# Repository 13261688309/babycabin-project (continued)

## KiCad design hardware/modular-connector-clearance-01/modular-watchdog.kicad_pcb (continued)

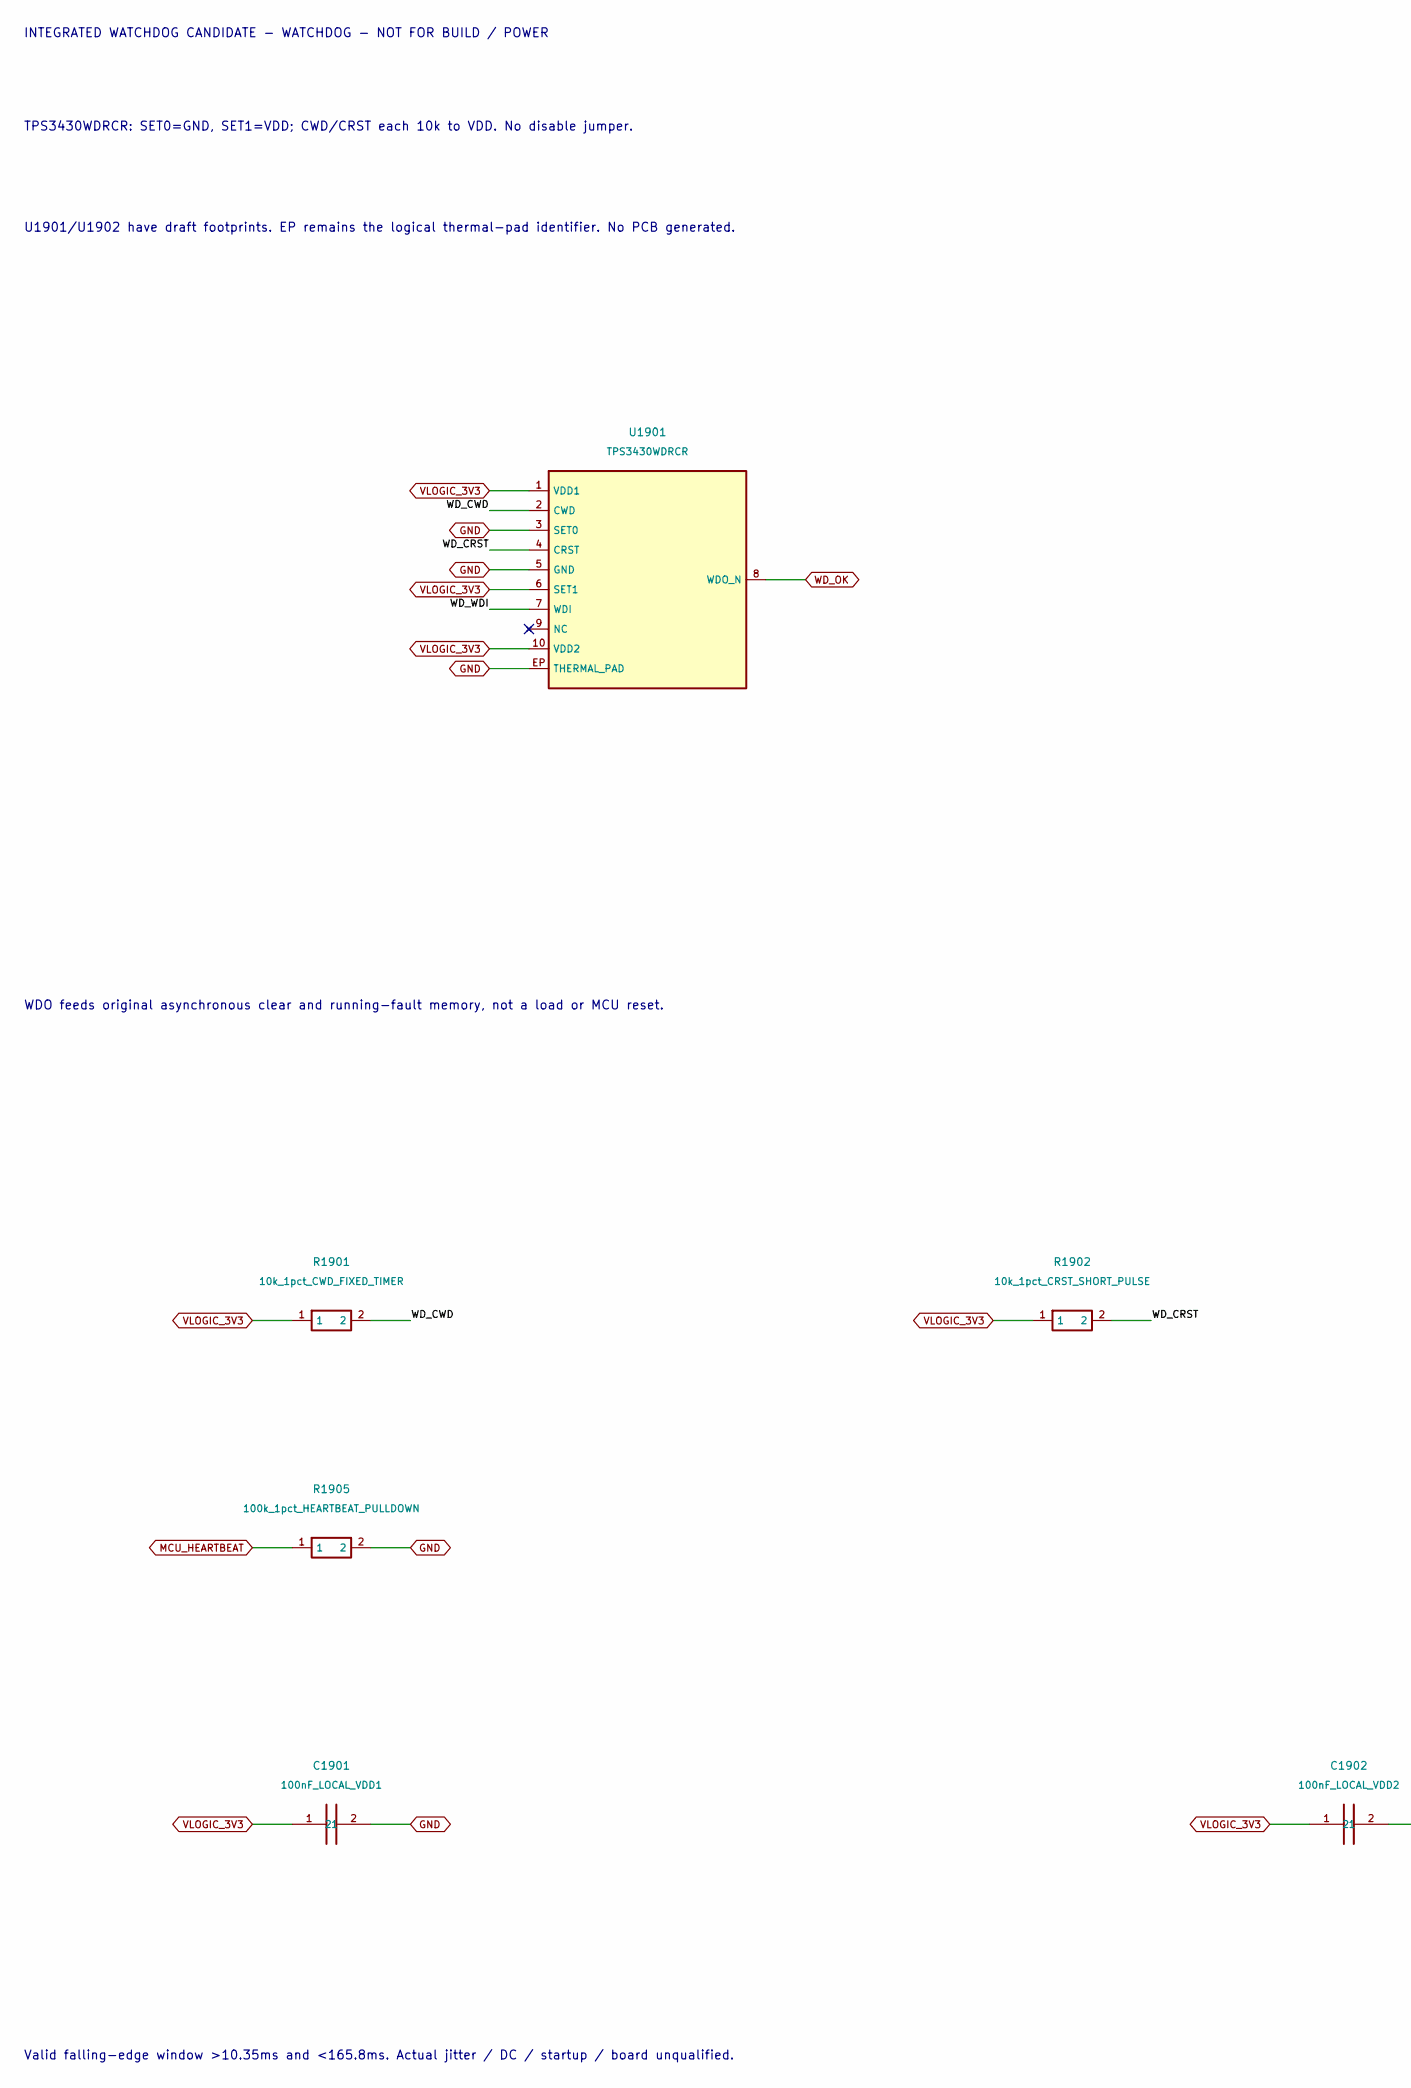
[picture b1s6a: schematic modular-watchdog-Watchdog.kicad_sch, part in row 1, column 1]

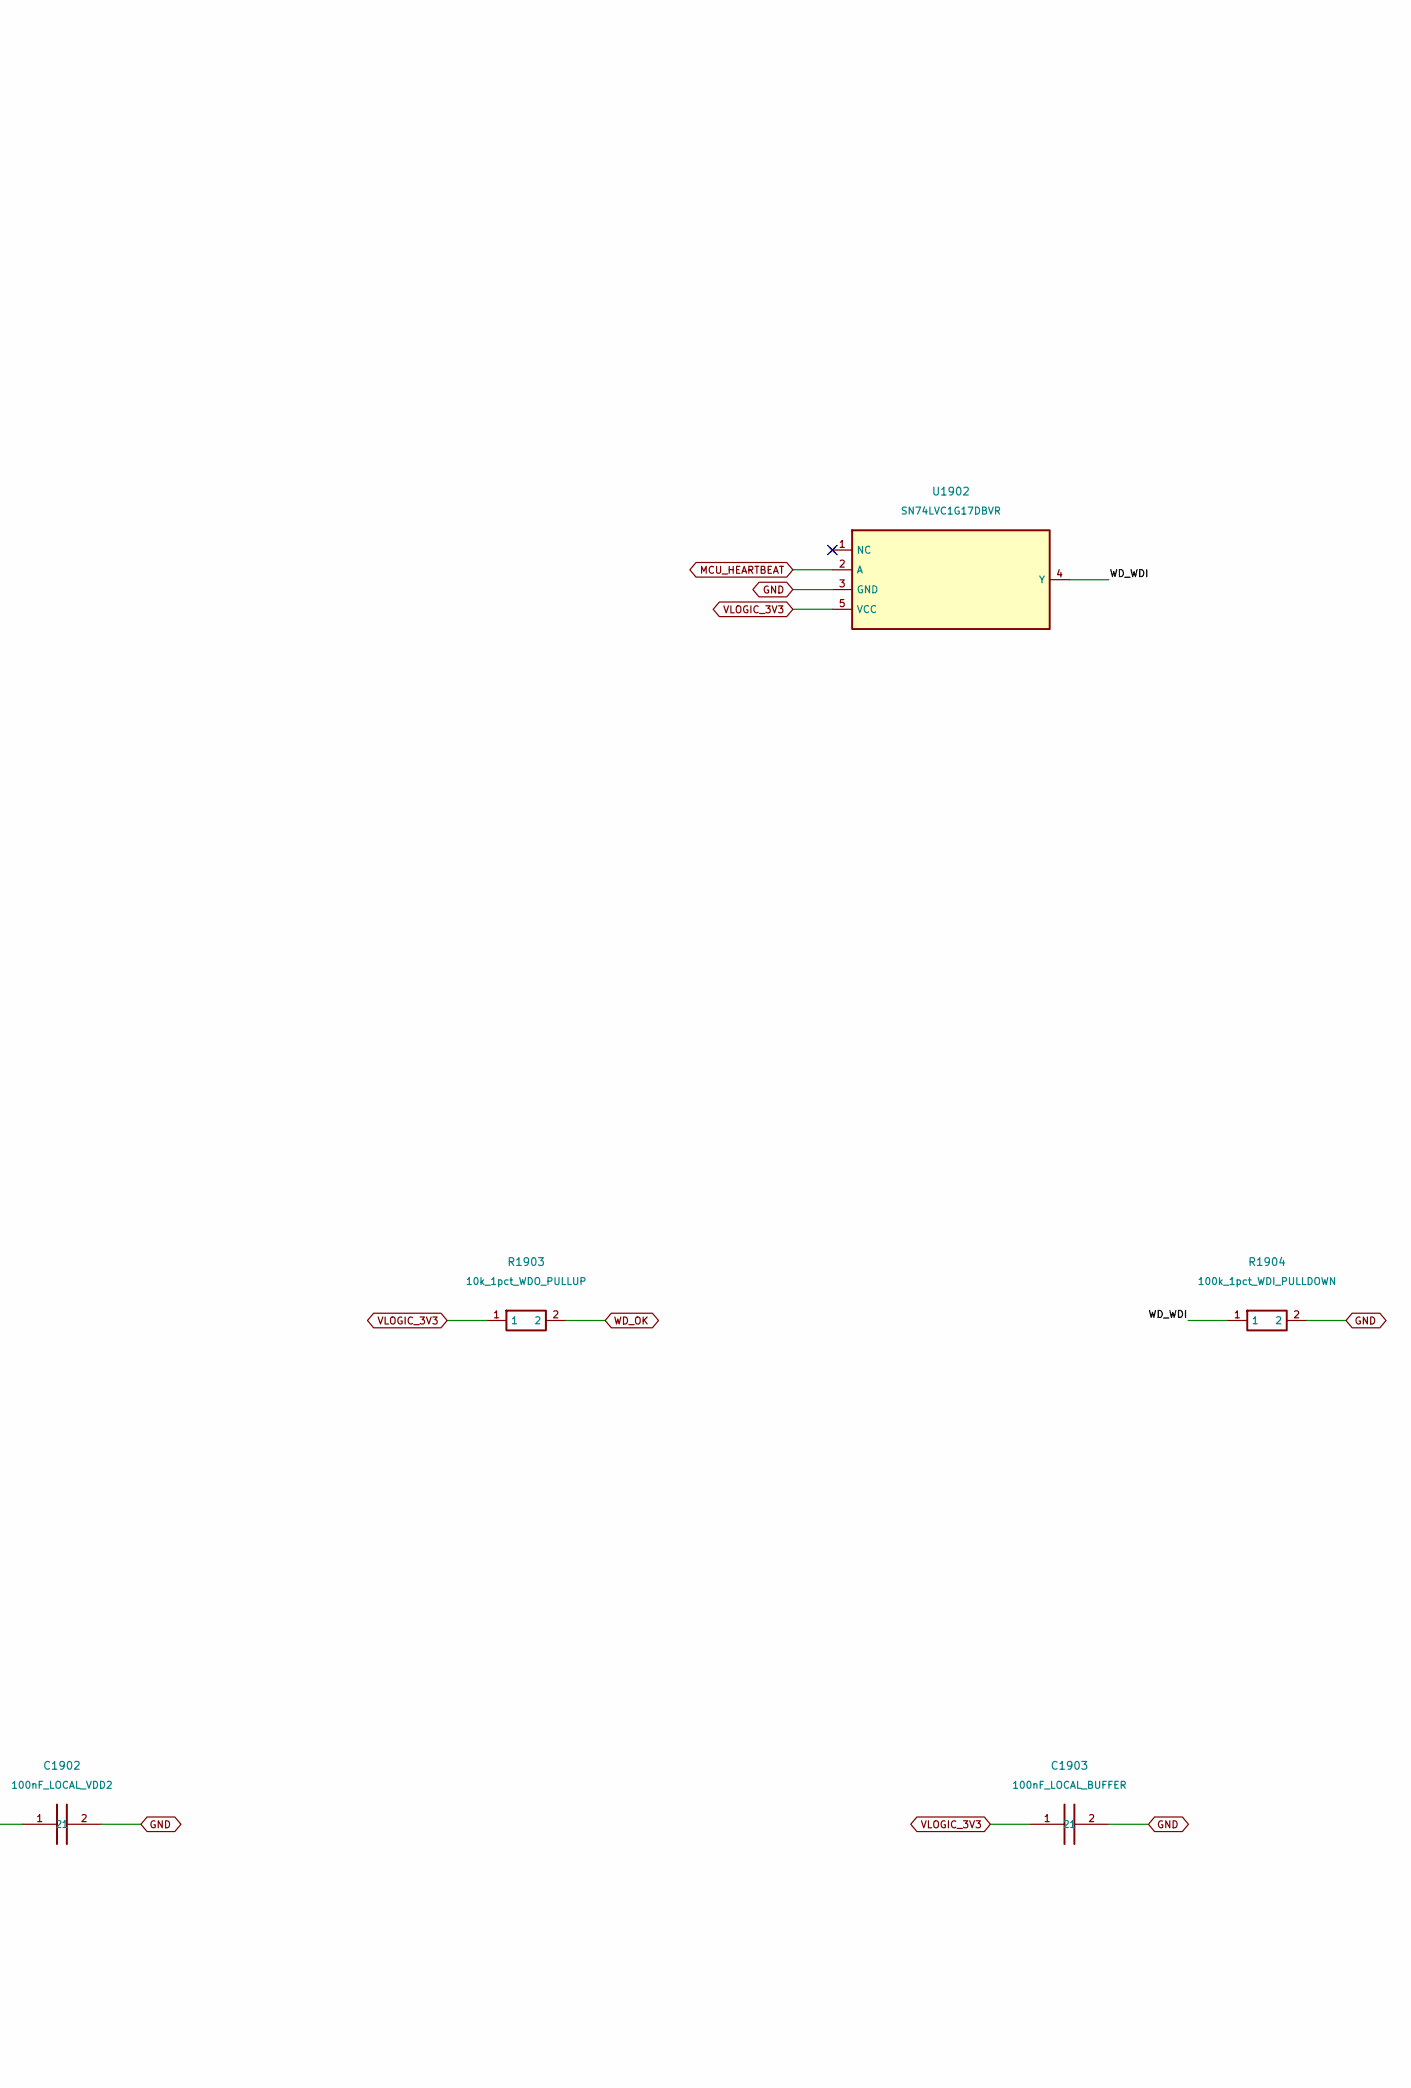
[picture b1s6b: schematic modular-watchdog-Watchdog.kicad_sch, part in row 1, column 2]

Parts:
C1901: 100nF_LOCAL_VDD1; TDK_0603_Reflow_CapacitorDraft
C1902: 100nF_LOCAL_VDD2; TDK_0603_Reflow_CapacitorDraft
C1903: 100nF_LOCAL_BUFFER; TDK_0603_Reflow_CapacitorDraft
R1901: 10k_1pct_CWD_FIXED_TIMER; Vishay_CRCW0805_Reflow_ResistorDraft
R1902: 10k_1pct_CRST_SHORT_PULSE; Vishay_CRCW0805_Reflow_ResistorDraft
R1903: 10k_1pct_WDO_PULLUP; Vishay_CRCW0805_Reflow_ResistorDraft
R1904: 100k_1pct_WDI_PULLDOWN; Vishay_CRCW0805_Reflow_ResistorDraft
R1905: 100k_1pct_HEARTBEAT_PULLDOWN; Vishay_CRCW0805_Reflow_ResistorDraft
U1901: TPS3430WDRCR; TI_DRC0010J_LogicalEP_WatchdogDraft
U1902: SN74LVC1G17DBVR; TI_DBV0005A_WatchdogDraft

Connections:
/Watchdog/WD_CRST: R1902.2, U1901.4 (CRST)
/Watchdog/WD_CWD: R1901.2, U1901.2 (CWD)
/Watchdog/WD_WDI: R1904.1, U1901.7 (WDI), U1902.4 (Y)
GND: C1901.2, C1902.2, C1903.2, R1904.2, R1905.2, U1901.3 (SET0), U1901.5 (GND), U1901.EP (THERMAL_PAD), U1902.3 (GND); also elsewhere on the board
MCU_HEARTBEAT: R1905.1, U1902.2 (A); also elsewhere on the board
VLOGIC_3V3: C1901.1, C1902.1, C1903.1, R1901.1, R1902.1, R1903.1, U1901.1 (VDD1), U1901.6 (SET1), U1901.10 (VDD2), U1902.5 (VCC); also elsewhere on the board
WD_OK: R1903.2, U1901.8 (WDO_N); also elsewhere on the board

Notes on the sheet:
INTEGRATED WATCHDOG CANDIDATE - WATCHDOG - NOT FOR BUILD / POWER
TPS3430WDRCR: SET0=GND, SET1=VDD; CWD/CRST each 10k to VDD. No disable jumper.
U1901/U1902 have draft footprints. EP remains the logical thermal-pad identifier. No PCB generated.
WDO feeds original asynchronous clear and running-fault memory, not a load or MCU reset.
Valid falling-edge window >10.35ms and <165.8ms. Actual jitter / DC / startup / board unqualified.

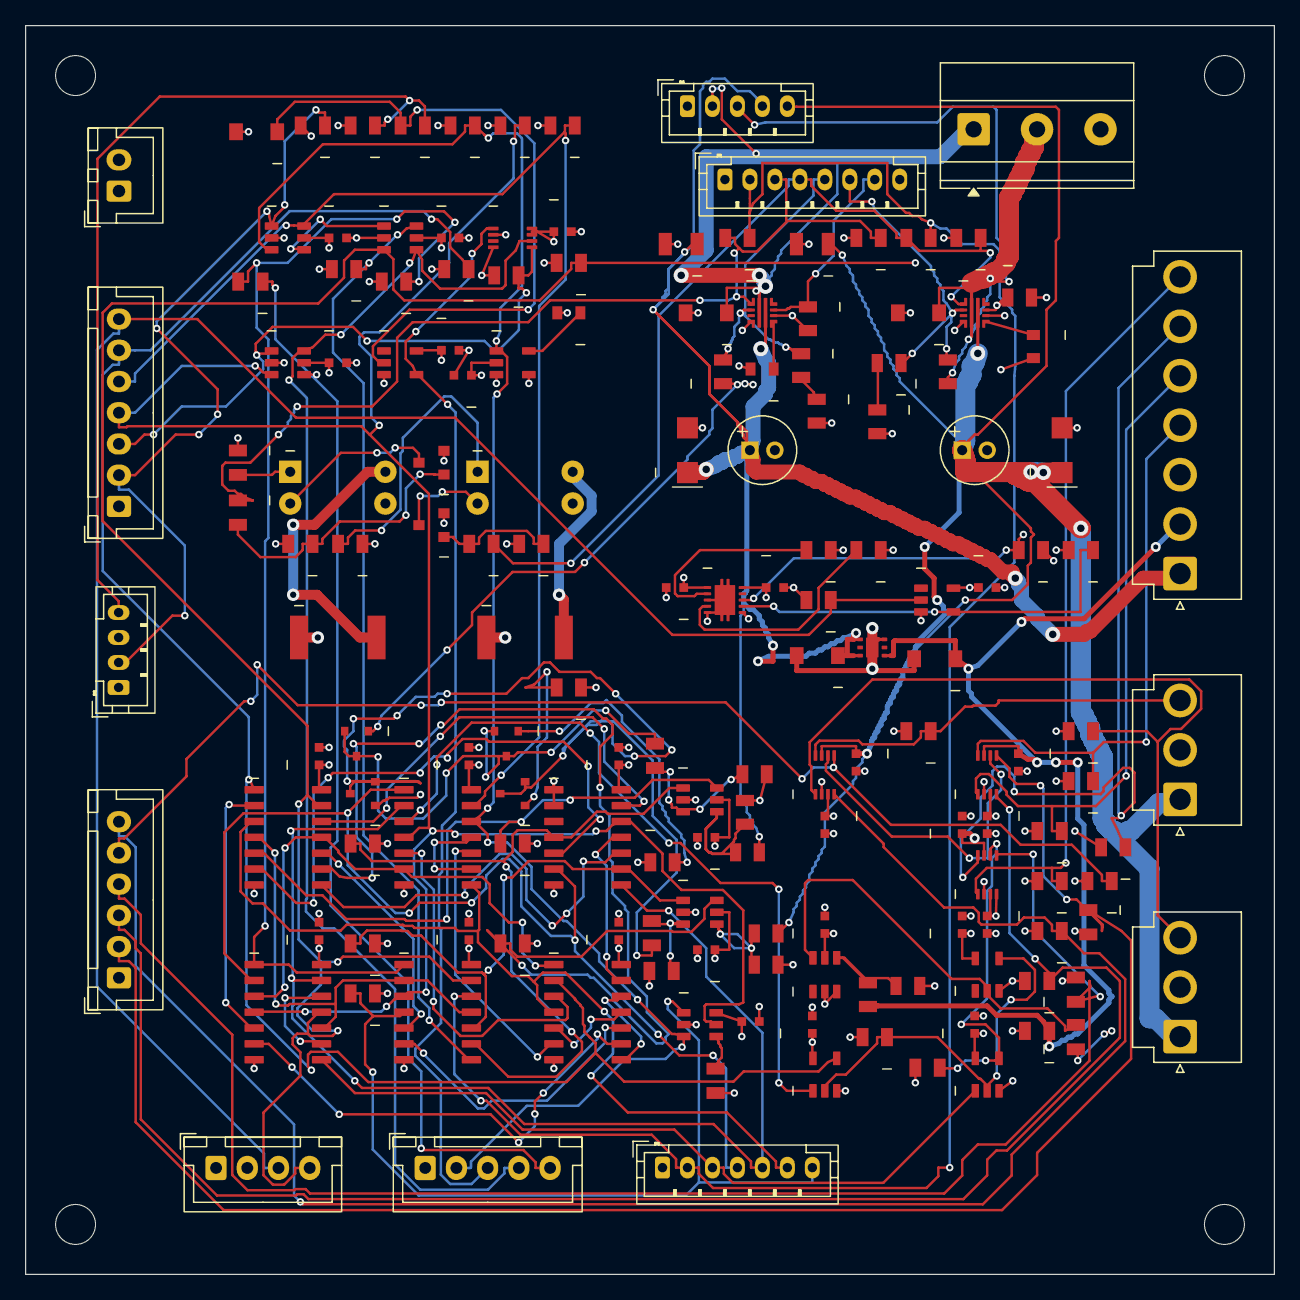
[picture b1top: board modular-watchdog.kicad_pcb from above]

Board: 4 copper layers, 100.0 x 100.0 mm, 164 parts (0 on the bottom side), 96 nets.

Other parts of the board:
H1, H2, H3, H4: MECHANICAL_NPTH_3.2_NOT_ELECTRICAL_BOM; NPTH_3.2_Keepout6.4
